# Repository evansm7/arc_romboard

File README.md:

# Acorn Archimedes ROM/flash carrier board

v1, 31 July 2021
(c) 2021 Matt Evans

Here lies an Eagle PCB design for a ROM carrier board for older Acorn Archimedes machines.  This board allows ROMs larger than the original RISC OS 2.00 DIP28 1Mbit ROMs to be fitted, including for RISC OS 3.11.

Typically, these carrier boards aren't needed for the A3000, A440/1 and later machines, but are used on A3xx/A4xx/R140 machines.  I will refer to this generation of machine as "A440".

This board also fettles pins that are write-enable on flash parts, so might also be useful for fitting flash to machines that ordinarily don't need a carrier board (such as A3000).

This board is verified working with DIP28 1Mbit ROMs (e.g. RISC OS 2.00), JEDEC DIP32 4Mbit flash (SST39SF040) and JEDEC DIP32 4Mbit ROMs (e.g. RISC OS 3.xx).

# Construction

## Materials required

  * One 3x1 0.1" pin header (JP1)
  * One 3x2 0.1" pin header (JP2)
  * Four good-quality turned-pin DIP32 sockets
  * Good-quality turned-pin SIL pins: four lots of 32 pins (128 total)
	* A minimalist version could use about 70
  * One 3x1 0.1" right-angle pin header (LA)
  * One SMT tantalum decoupling cap (optional)

## Circuit

This board is more or less the same as the commercial/Acorn ROM carrier boards, except this board also supports 4 megabit flash chips having /WE on pin 31, pulled high.  (Some commercial boards may do, too?)

Three address lines, LA[20:18], need to be provided from the motherboard.  Although LA18 might be provided from the ROM sockets already, its presence and location depends on the configuration of the motherboard jumpers (LK12 on A440).  It is easier/cleaner to just provide one more wire and not depend on correct jumper configuration.

The motherboard LK2 and LK6 links (on A440) are assumed to be in their default "b" position, providing LA16 and LA17 to the ROM sockets.

## Soldering

You will notice that there's a chicken and egg problem:  if you solder on the sockets first, you can't reach under the sockets (unless you use SIL turned-pin sockets) to solder the SIL pins.

Solder the SIL pins in first, taking care to keep them straight.  Temporarily plugging them into a spare DIL socket whilst soldering them can help get the spacing and alignment correct.  You then have to solder some of the DIL socket pins _between_ adjacent rows of SIL pins, which is kinda tricky.  You'll need a narrow bit -- for example, a Weller 0.5mm bit is pointy enough to reach, just.

Note:  Not all 'downward' SIL pins are required, as most of the ROM socket pins are common except for the per-chip data pins.  More is better for mechanical stability and redundancy in crusty 1980s sockets, but for example one could fully populate the left and right sockets, then fill only the data pins (pins 13-21 including ground) in the middle two sockets.  That makes 82 total.

Remember to fill the solder jumper on the bottom (on the side of the silkscreen bar)!

## Configuring jumpers

The following memory types are supported:

  * Non-JEDEC DIP28 1Mbit ROM
	* Pin 24 (A16) = LA18, pin 30 = Vcc
  * JEDEC DIP32 4Mbit ROM
	* Pin 24 (/OE) = Gnd, pin 30 (A17) = LA19, pin 1 (Vpp) = Vcc, pin 31 (A18) = LA20
  * JEDEC DIP32 4Mbit flash
	* Pin 24 (/OE) = Gnd, pin 30 (A17) = LA19, pin 1 (A18) = LA20, pin 31 (/WE) = Vcc

Generally, pin 2 is A16 (connected to LA18 via a semi-permanent solder jumper), but some DIP32 1Mbit ROMs (e.g. 27C301) use /OE on pin 2.
It's not worth having a regular jumper for these (1Mb pffft), but the option's there via a bodge wire from the solder jumper.

# Installation

The SIL pins on the bottom plug into the four ROM sockets, taking care with alignment and orientation.  The LA pin header should point "south" on the motherboard (see the nearby legend).

Three jumper wires are required to be soldered to the motherboard to pick up LA[20:18].

On an A440, this is most easily achieved using short wires to IC28 (to the south of the backplane socket):

   * IC28 pin 18 = LA18
   * IC28 pin 17 = LA19
   * IC28 pin 16 = LA20

Wire these, via about 5cm of wire, to a 3-way socket e.g. of the crimp pin/"DuPont" variety.

Don't worry, if you get the address wires plugged on backwards, nothing will explode.  But, the machine will only boot if it's installed correctly.  :-)

# License

This work is licenced under the Creative Commons [CC BY-SA 3.0](https://creativecommons.org/licenses/by-sa/3.0/) license.

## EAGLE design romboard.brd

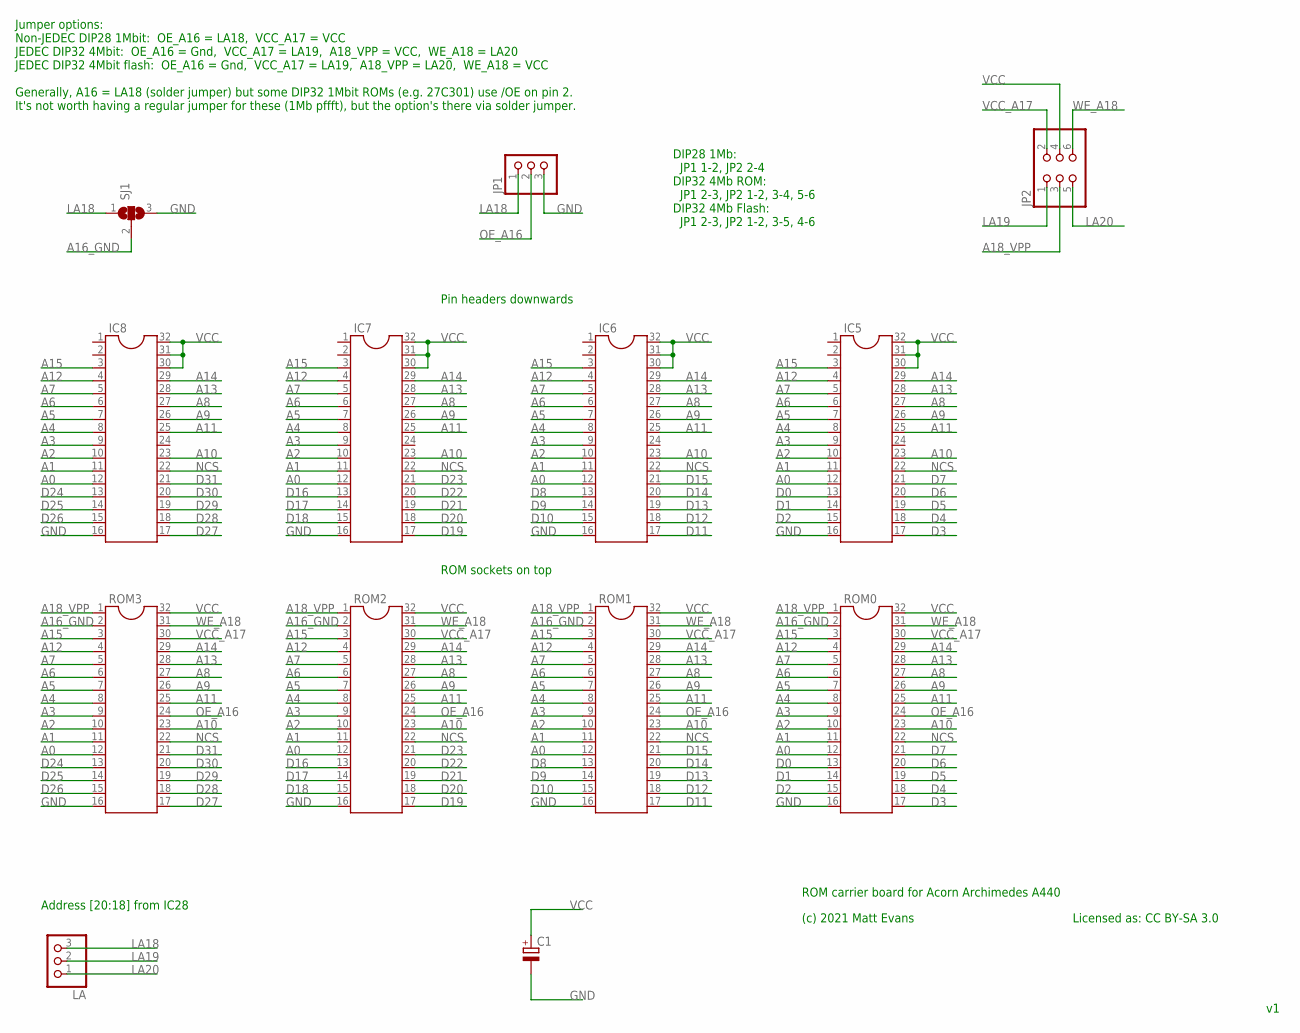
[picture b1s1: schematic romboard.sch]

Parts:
C1: CPOL-EU085CS-1AR; 085CS_1AR
IC5, IC6, IC7, IC8: DIL32
JP1: PINHD-1X3; 1X03
JP2: PINHD-2X3; 2X03
LA: PINHD-1X3/90; 1X03/90
ROM0, ROM1, ROM2, ROM3: DIL32
SJ1: SJ2W; SJ_2

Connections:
A0: IC5.12, IC6.12, IC7.12, IC8.12, ROM0.12, ROM1.12, ROM2.12, ROM3.12
A1: IC5.11, IC6.11, IC7.11, IC8.11, ROM0.11, ROM1.11, ROM2.11, ROM3.11
A2: IC5.10, IC6.10, IC7.10, IC8.10, ROM0.10, ROM1.10, ROM2.10, ROM3.10
A3: IC5.9, IC6.9, IC7.9, IC8.9, ROM0.9, ROM1.9, ROM2.9, ROM3.9
A4: IC5.8, IC6.8, IC7.8, IC8.8, ROM0.8, ROM1.8, ROM2.8, ROM3.8
A5: IC5.7, IC6.7, IC7.7, IC8.7, ROM0.7, ROM1.7, ROM2.7, ROM3.7
A6: IC5.6, IC6.6, IC7.6, IC8.6, ROM0.6, ROM1.6, ROM2.6, ROM3.6
A7: IC5.5, IC6.5, IC7.5, IC8.5, ROM0.5, ROM1.5, ROM2.5, ROM3.5
A8: IC5.27, IC6.27, IC7.27, IC8.27, ROM0.27, ROM1.27, ROM2.27, ROM3.27
A9: IC5.26, IC6.26, IC7.26, IC8.26, ROM0.26, ROM1.26, ROM2.26, ROM3.26
A10: IC5.23, IC6.23, IC7.23, IC8.23, ROM0.23, ROM1.23, ROM2.23, ROM3.23
A11: IC5.25, IC6.25, IC7.25, IC8.25, ROM0.25, ROM1.25, ROM2.25, ROM3.25
A12: IC5.4, IC6.4, IC7.4, IC8.4, ROM0.4, ROM1.4, ROM2.4, ROM3.4
A13: IC5.28, IC6.28, IC7.28, IC8.28, ROM0.28, ROM1.28, ROM2.28, ROM3.28
A14: IC5.29, IC6.29, IC7.29, IC8.29, ROM0.29, ROM1.29, ROM2.29, ROM3.29
A15: IC5.3, IC6.3, IC7.3, IC8.3, ROM0.3, ROM1.3, ROM2.3, ROM3.3
A16_GND: ROM0.2, ROM1.2, ROM2.2, ROM3.2, SJ1.2
A18_VPP: JP2.3, ROM0.1, ROM1.1, ROM2.1, ROM3.1
D0: IC5.13, ROM0.13
D1: IC5.14, ROM0.14
D2: IC5.15, ROM0.15
D3: IC5.17, ROM0.17
D4: IC5.18, ROM0.18
D5: IC5.19, ROM0.19
D6: IC5.20, ROM0.20
D7: IC5.21, ROM0.21
D8: IC6.13, ROM1.13
D9: IC6.14, ROM1.14
D10: IC6.15, ROM1.15
D11: IC6.17, ROM1.17
D12: IC6.18, ROM1.18
D13: IC6.19, ROM1.19
D14: IC6.20, ROM1.20
D15: IC6.21, ROM1.21
D16: IC7.13, ROM2.13
D17: IC7.14, ROM2.14
D18: IC7.15, ROM2.15
D19: IC7.17, ROM2.17
D20: IC7.18, ROM2.18
D21: IC7.19, ROM2.19
D22: IC7.20, ROM2.20
D23: IC7.21, ROM2.21
D24: IC8.13, ROM3.13
D25: IC8.14, ROM3.14
D26: IC8.15, ROM3.15
D27: IC8.17, ROM3.17
D28: IC8.18, ROM3.18
D29: IC8.19, ROM3.19
D30: IC8.20, ROM3.20
D31: IC8.21, ROM3.21
GND: C1.-, IC5.16, IC6.16, IC7.16, IC8.16, JP1.3, ROM0.16, ROM1.16, ROM2.16, ROM3.16, SJ1.3
LA18: JP1.1, LA.3, SJ1.1
LA19: JP2.1, LA.2
LA20: JP2.5, LA.1
NCS: IC5.22, IC6.22, IC7.22, IC8.22, ROM0.22, ROM1.22, ROM2.22, ROM3.22
OE_A16: JP1.2, ROM0.24, ROM1.24, ROM2.24, ROM3.24
VCC: C1.+, IC5.30, IC5.31, IC5.32, IC6.30, IC6.31, IC6.32, IC7.30, IC7.31, IC7.32, IC8.30, IC8.31, IC8.32, JP2.4, ROM0.32, ROM1.32, ROM2.32, ROM3.32
VCC_A17: JP2.2, ROM0.30, ROM1.30, ROM2.30, ROM3.30
WE_A18: JP2.6, ROM0.31, ROM1.31, ROM2.31, ROM3.31

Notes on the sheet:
Pin headers downwards
ROM sockets on top
Address [20:18] from IC28
Jumper options: Non-JEDEC DIP28 1Mbit: OE_A16 = LA18, VCC_A17 = VCC JEDEC DIP32 4Mbit: OE_A16 = Gnd, VCC_A17 = LA19, A18_VPP = VCC, WE_A18 = LA20 JEDEC DIP32 4Mbit flash: OE_A16 = Gnd, VCC_A17 = LA19, A18_VPP = LA20, WE_A18 = VCC Generally, A16 = LA18 (solder jumper) but some DIP32 1Mbit ROMs (e.g.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
ROM carrier board for Acorn Archimedes A440
(c) 2021 Matt Evans
DIP28 1Mb: JP1 1-2, JP2 2-4 DIP32 4Mb ROM: JP1 2-3, JP2 1-2, 3-4, 5-6 DIP32 4Mb Flash: JP1 2-3, JP2 1-2, 3-5, 4-6
Licensed as: CC BY-SA 3.0

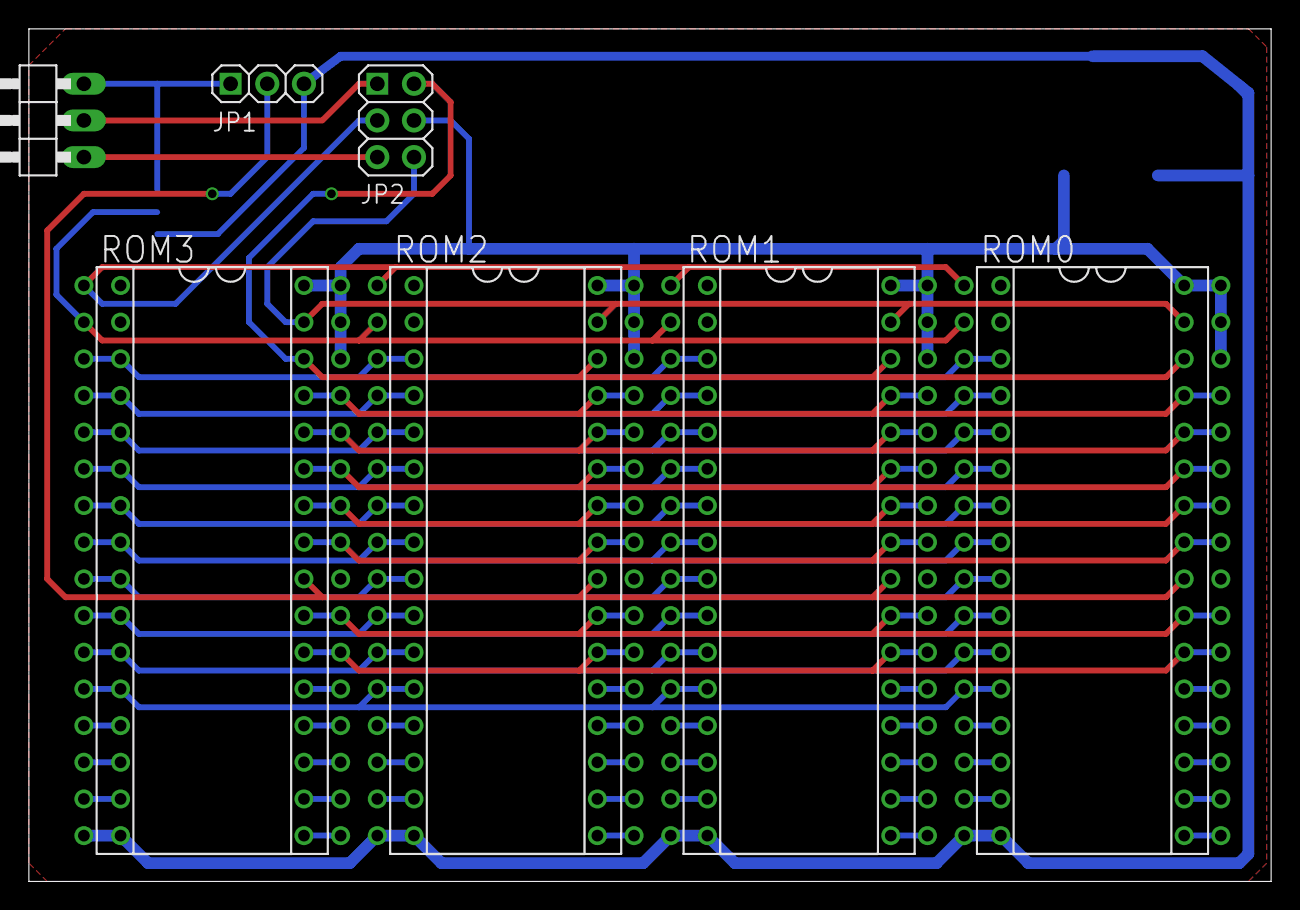
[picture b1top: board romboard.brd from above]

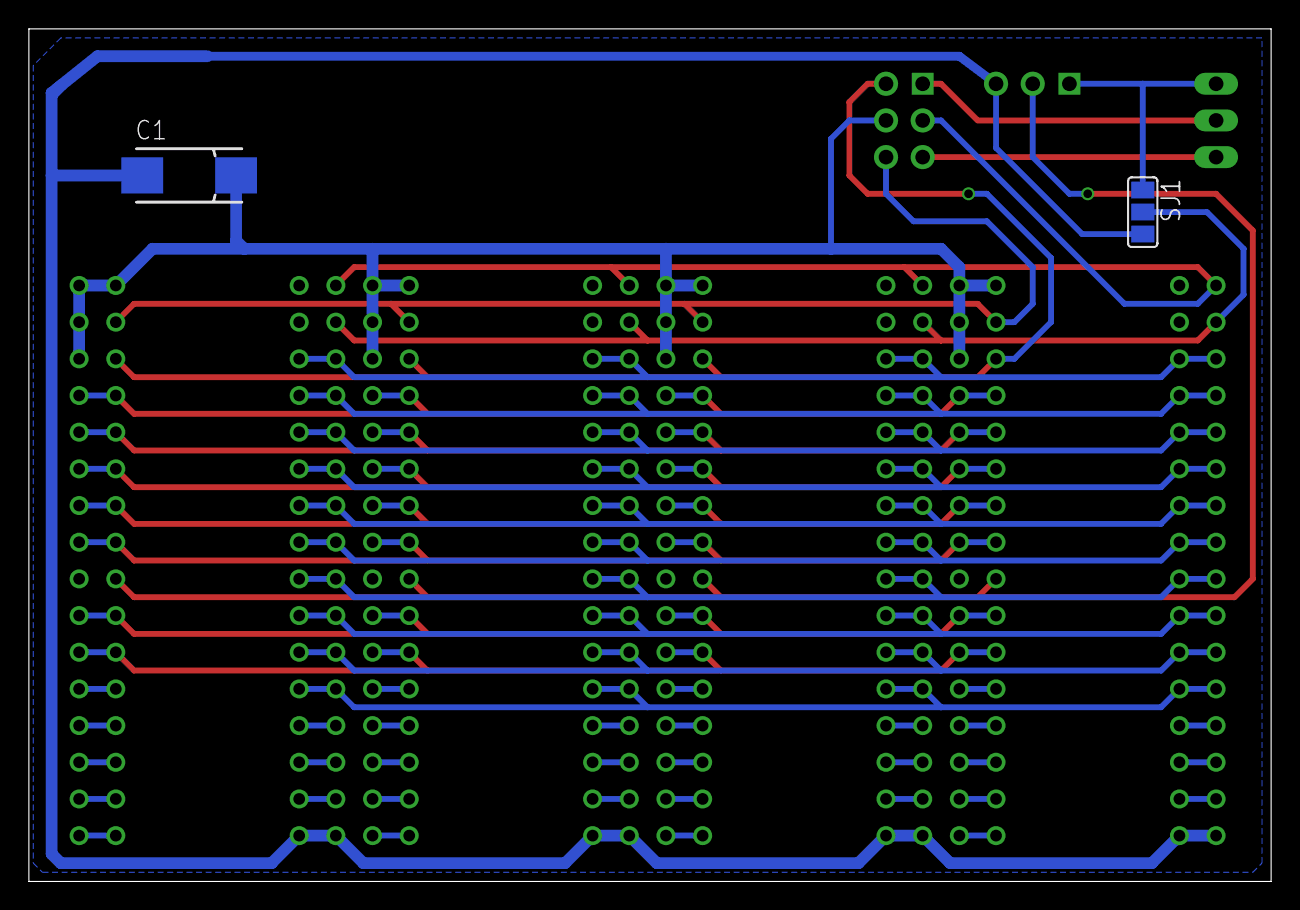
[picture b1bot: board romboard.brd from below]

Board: 2 copper layers, 86.0 x 59.0 mm, 13 parts (2 on the bottom side), 59 nets.

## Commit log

2021-07-31 First commit: v1 schematic & routed
2021-07-31 Add Gnd pours, tweak silkscreen
2021-08-24 Add licence to schematic, board
2021-08-24 Add README
